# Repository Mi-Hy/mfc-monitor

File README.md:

### 1️⃣ Adjust time to UTC and enable RTC
- `sudo raspi-config`
- `5 Localisation Options` --> `L2 Timezone` --> `None of the above` --> `UTC`
- Reboot Pi `sudo reboot`

### 2️⃣ Create SSH Key to clone this repository
- On the raspberry pi
	```
	ssh-keygen -t ed25519 -C "jarne.vanmulders@kuleuven.be"
	cat ~/.ssh/id_ed25519.pub
	```
- ENTER 3x
- Add key to github account [online] --> settings --> SSH Key
- Clone repo via SSH
- Install git
	```
	sudo apt update
	sudo apt install git -y
	```
- Git clone via SSH KEY on rpi in home dir: `git clone git@github.com:Mi-Hy/mfc-monitor-hw2.git`

### 3️⃣ Enable I2C
- `sudo raspi-config`
- `3 Interface Options` --> `I5 I2C` --> `Yes`
- Check devices on I2C bus
  ```
  sudo apt update
  sudo apt install i2c-tools
  sudo i2cdetect -y 1
  ```
### 4️⃣ Check energy profiler
- Install screen
	```
	sudo apt update
	sudo apt install screen
	```
- `screen /dev/ttyUSB0 115200`

### 5️⃣ Connection with temperature sensors DS18B20
1. Connect D to GPIO4
2. Enable w1-gpio: add `dtoverlay=w1-gpio` with `sudo nano /boot/firmware/config.txt`
3. Reboot `sudo reboot`
4. Activate and test onewire:
	``` 
	sudo modprobe w1-gpio
	sudo modprobe w1-therm
	cd /sys/bus/w1/devices
	ls
	``` 
	If you see the sensor's ID as dir here, all is well. 

### 6️⃣ Install required python packages
Install pip `sudo apt install python3-pip`
```
sudo python3 -m pip install pyyaml --break-system-packages
sudo python3 -m pip install filelock --break-system-packages
sudo python3 -m pip install influxdb_client --break-system-packages
sudo python3 -m pip install flask --break-system-packages
sudo python3 -m pip install psutil --break-system-packages
sudo python3 -m pip install pyserial --break-system-packages
``` 
### 7️⃣ Test all individual scripts
1. Test `system.py`
2. Test `voltages.py`
3. Test `load.py`
4. Test `controller.py`
5. Run services
	1. Copy service files to systemd:
	```
	sudo cp ~/mfc-monitor/controller.service /lib/systemd/system/
 	```
 	2. Enable and start services
  	```
   	sudo systemctl enable controller.service
   	sudo systemctl start controller.service
  	```
   	3. Logs
    ```
   	sudo journalctl -u controller.service -f
    ```
   	4. After updates
	```
	sudo systemctl daemon-reload
	sudo systemctl restart controller.service
 	```

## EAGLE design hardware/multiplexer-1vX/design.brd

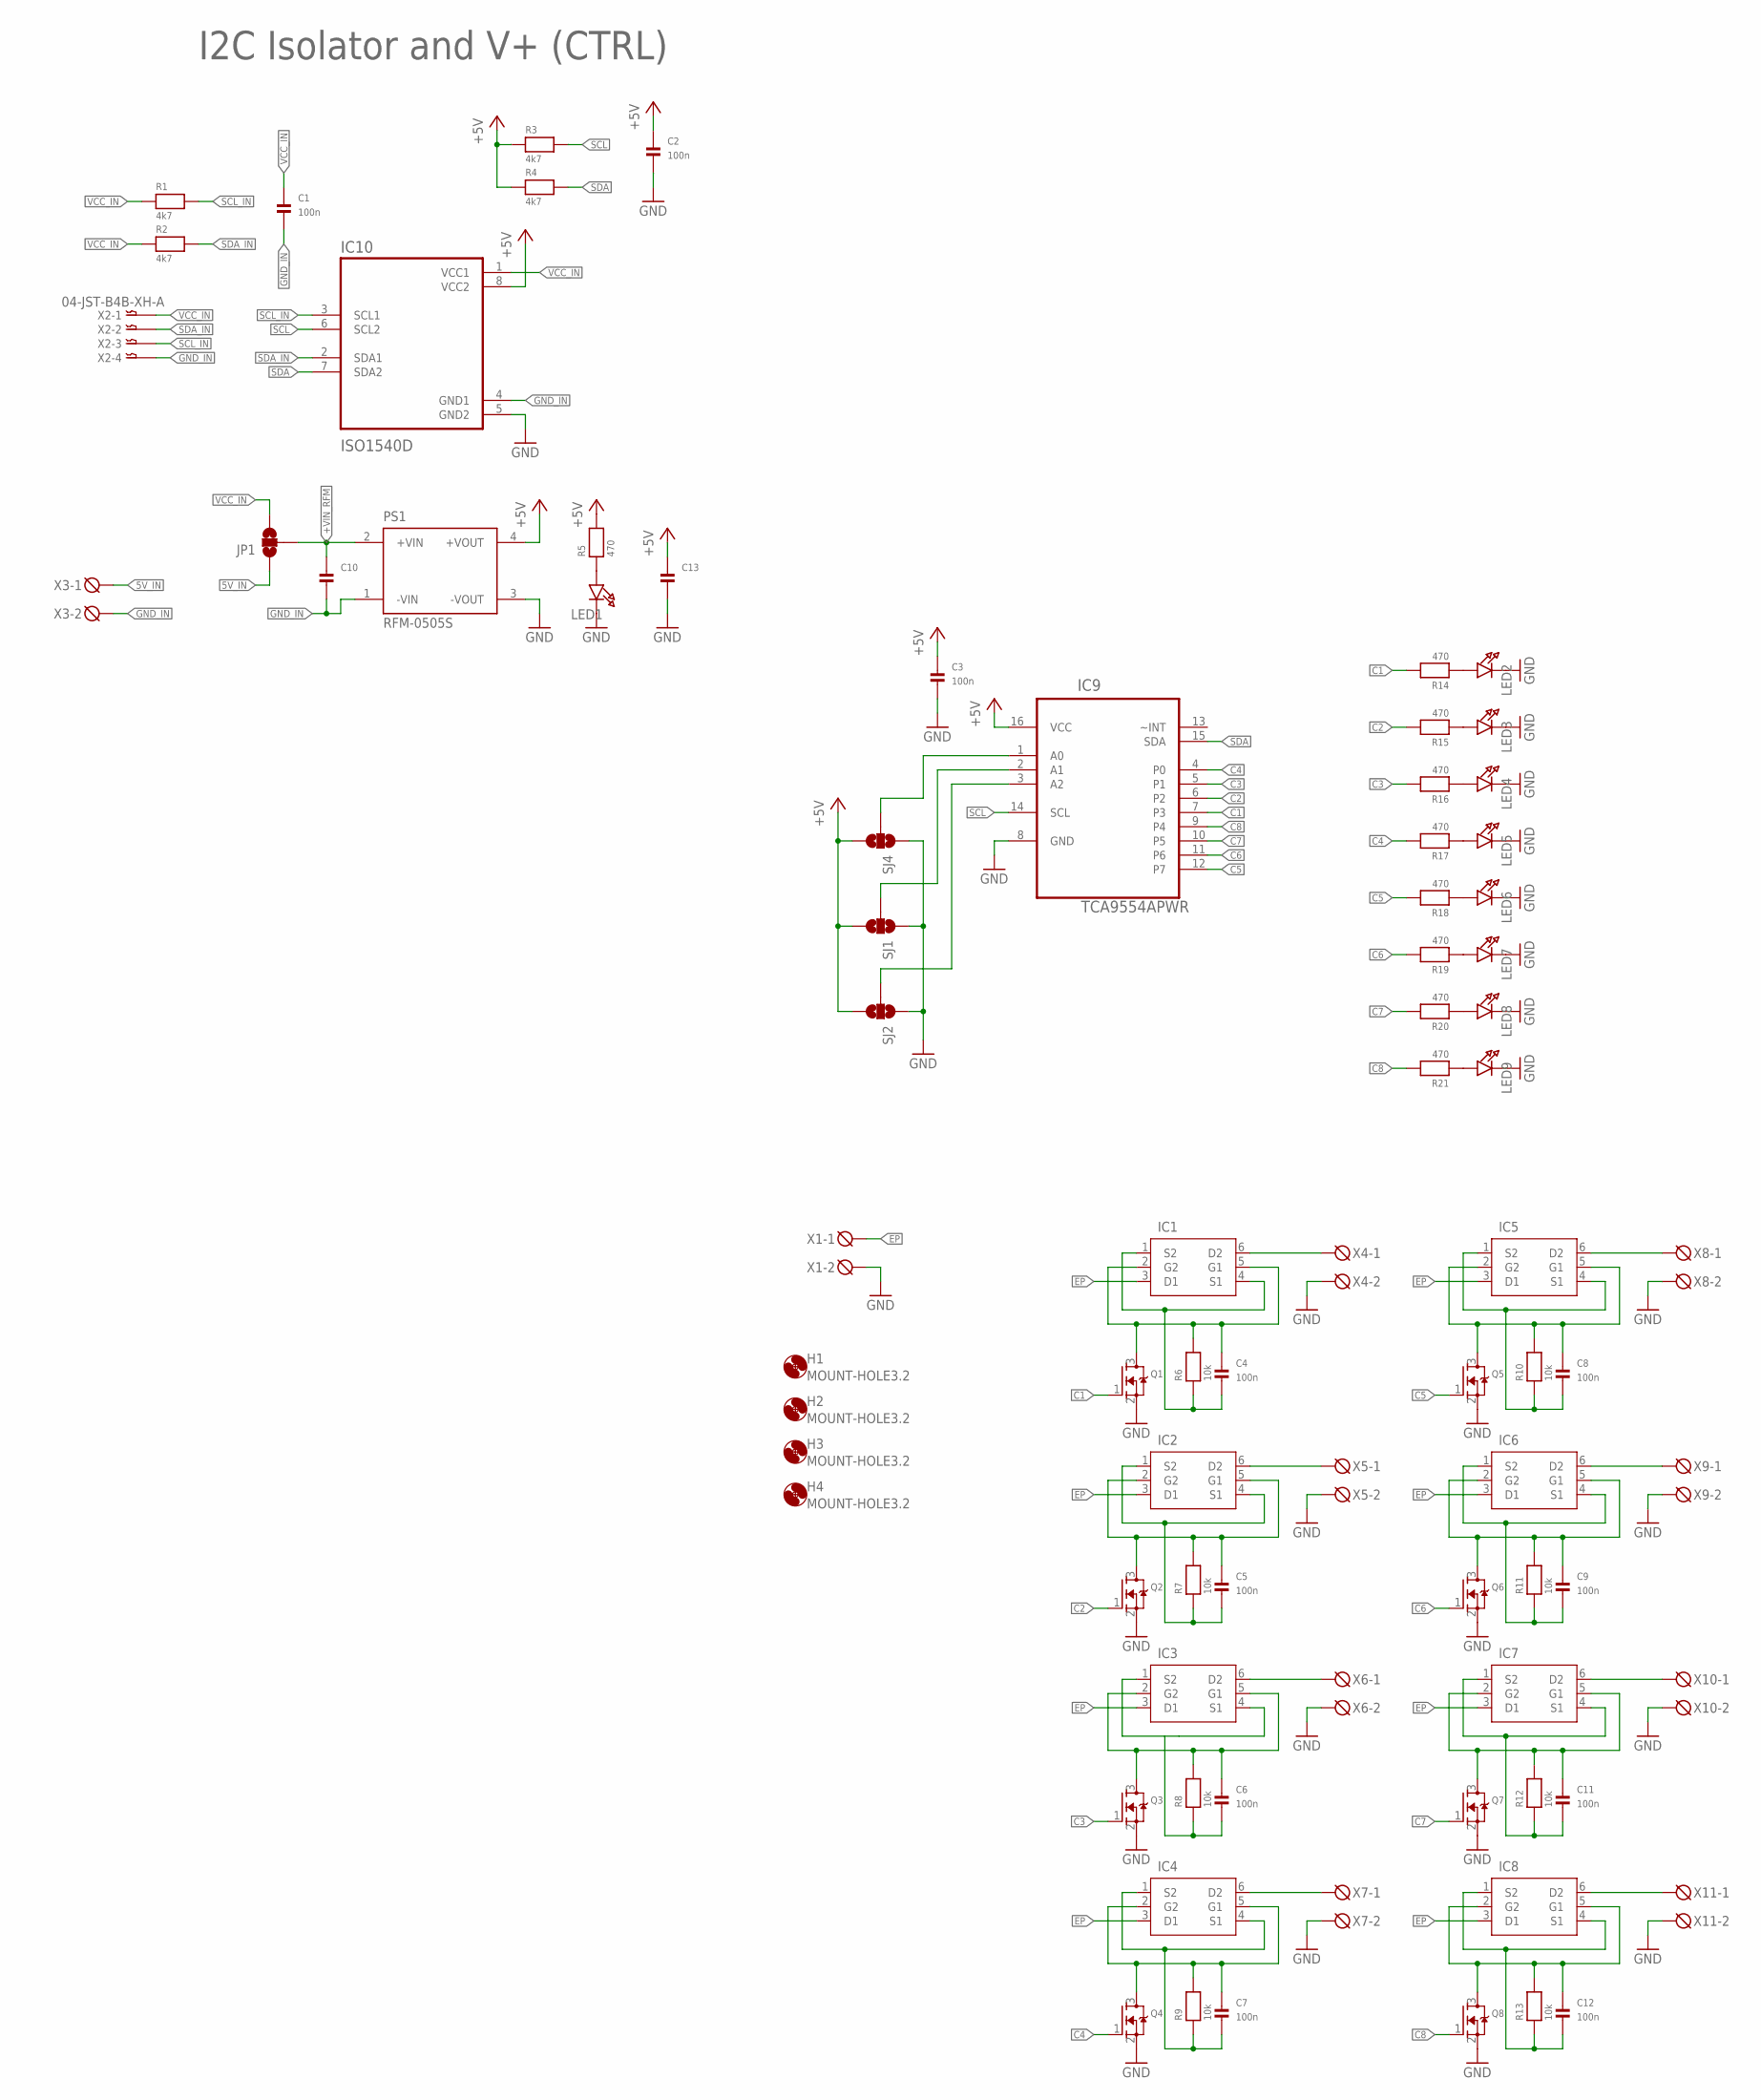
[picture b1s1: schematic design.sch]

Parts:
C1, C2, C3, C4, C5, C6, C7, C8, C9, C11, C12: 100n; 0603
C10, C13: CAP_CERAMIC0805; 0805
H1, H2, H3, H4: MOUNT-HOLE3.2; 3,2
IC1, IC2, IC3, IC4, IC5, IC6, IC7, IC8: DMP2200UDW; SOT65P210X110-6N
IC9: TCA9554APWR; SOP65P640X120-16N
IC10: ISO1540D; SOIC127P599X175-8N
JP1: JUMPER-SMT_3_NO_SILK; SMT-JUMPER_3_NO_SILK
LED1, LED2, LED3, LED4, LED5, LED6, LED7, LED8, LED9: LED0805; CHIPLED_0805
PS1: RFM-0505S; CONV_RFM-0505S
Q1, Q2, Q3, Q4, Q5, Q6, Q7, Q8: MOSFET-NREFLOW; SOT23-R
R1, R2, R3, R4: 4k7; 0603
R5, R14, R15, R16, R17, R18, R19, R20, R21: 470; 0603
R6, R7, R8, R9, R10, R11, R12, R13: 10k; 0603
SJ1, SJ2, SJ4: SOLDERJUMPER_2WAYS; SJ_3
X1, X3, X4, X5, X6, X7, X8, X9, X10, X11: DG3XX-02-5.0; DG306-5.0-02P
X2: 04-JST-B4B-XH-A; B4B-XH

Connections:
5V_IN: JP1.1, X3.1
+5V: C2.1, C3.1, C13.1, IC9.16 (VCC), IC10.8 (VCC2), PS1.4 (+VOUT), R3.1, R4.1, R5.2, SJ1.3, SJ2.3, SJ4.3
+VIN_RFM: C10.1, JP1.2, PS1.2 (+VIN)
C1: IC9.7 (P3), Q1.1 (G), R14.2
C2: IC9.6 (P2), Q2.1 (G), R15.2
C3: IC9.5 (P1), Q3.1 (G), R16.2
C4: IC9.4 (P0), Q4.1 (G), R17.2
C5: IC9.12 (P7), Q5.1 (G), R18.2
C6: IC9.11 (P6), Q6.1 (G), R19.2
C7: IC9.10 (P5), Q7.1 (G), R20.2
C8: IC9.9 (P4), Q8.1 (G), R21.2
EP: IC1.3 (D1), IC2.3 (D1), IC3.3 (D1), IC4.3 (D1), IC5.3 (D1), IC6.3 (D1), IC7.3 (D1), IC8.3 (D1), X1.1
GND: C2.2, C3.2, C13.2, IC9.8 (GND), IC10.5 (GND2), LED1.C, LED2.C, LED3.C, LED4.C, LED5.C, LED6.C, LED7.C, LED8.C, LED9.C, PS1.3 (-VOUT), Q1.2 (S), Q2.2 (S), Q3.2 (S), Q4.2 (S), Q5.2 (S), Q6.2 (S), Q7.2 (S), Q8.2 (S), SJ1.1, SJ2.1, SJ4.1, X1.2, X4.2, X5.2, X6.2, X7.2, X8.2, X9.2, X10.2, X11.2
GND_IN: C1.2, C10.2, IC10.4 (GND1), PS1.1 (-VIN), X2.P$4, X3.2
unnamed: C4.1, IC1.2 (G2), IC1.5 (G1), Q1.3 (D), R6.2
unnamed: C4.2, IC1.1 (S2), IC1.4 (S1), R6.1
unnamed: C5.1, IC2.2 (G2), IC2.5 (G1), Q2.3 (D), R7.2
unnamed: IC1.6 (D2), X4.1
unnamed: IC9.1 (A0), SJ4.2
unnamed: IC9.2 (A1), SJ1.2
unnamed: IC9.3 (A2), SJ2.2
unnamed: IC2.6 (D2), X5.1
unnamed: C5.2, IC2.1 (S2), IC2.4 (S1), R7.1
unnamed: IC3.6 (D2), X6.1
unnamed: C6.2, IC3.1 (S2), IC3.4 (S1), R8.1
unnamed: IC4.6 (D2), X7.1
unnamed: C7.2, IC4.1 (S2), IC4.4 (S1), R9.1
unnamed: IC5.6 (D2), X8.1
unnamed: C8.2, IC5.1 (S2), IC5.4 (S1), R10.1
unnamed: IC6.6 (D2), X9.1
unnamed: C9.2, IC6.1 (S2), IC6.4 (S1), R11.1
unnamed: C11.1, IC7.2 (G2), IC7.5 (G1), Q7.3 (D), R12.2
unnamed: LED1.A, R5.1
unnamed: IC7.6 (D2), X10.1
unnamed: C11.2, IC7.1 (S2), IC7.4 (S1), R12.1
unnamed: IC8.6 (D2), X11.1
unnamed: C12.2, IC8.1 (S2), IC8.4 (S1), R13.1
unnamed: LED2.A, R14.1
unnamed: LED3.A, R15.1
unnamed: LED4.A, R16.1
unnamed: LED5.A, R17.1
unnamed: LED6.A, R18.1
unnamed: LED7.A, R19.1
unnamed: LED8.A, R20.1
unnamed: LED9.A, R21.1
unnamed: C6.1, IC3.2 (G2), IC3.5 (G1), Q3.3 (D), R8.2
unnamed: C7.1, IC4.2 (G2), IC4.5 (G1), Q4.3 (D), R9.2
unnamed: C12.1, IC8.2 (G2), IC8.5 (G1), Q8.3 (D), R13.2
unnamed: C9.1, IC6.2 (G2), IC6.5 (G1), Q6.3 (D), R11.2
unnamed: C8.1, IC5.2 (G2), IC5.5 (G1), Q5.3 (D), R10.2
SCL: IC9.14 (SCL), IC10.6 (SCL2), R3.2
SCL_IN: IC10.3 (SCL1), R1.2, X2.P$3
SDA: IC9.15 (SDA), IC10.7 (SDA2), R4.2
SDA_IN: IC10.2 (SDA1), R2.2, X2.P$2
VCC_IN: C1.1, IC10.1 (VCC1), JP1.3, R1.1, R2.1, X2.P$1

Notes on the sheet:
I2C Isolator and V+ (CTRL)

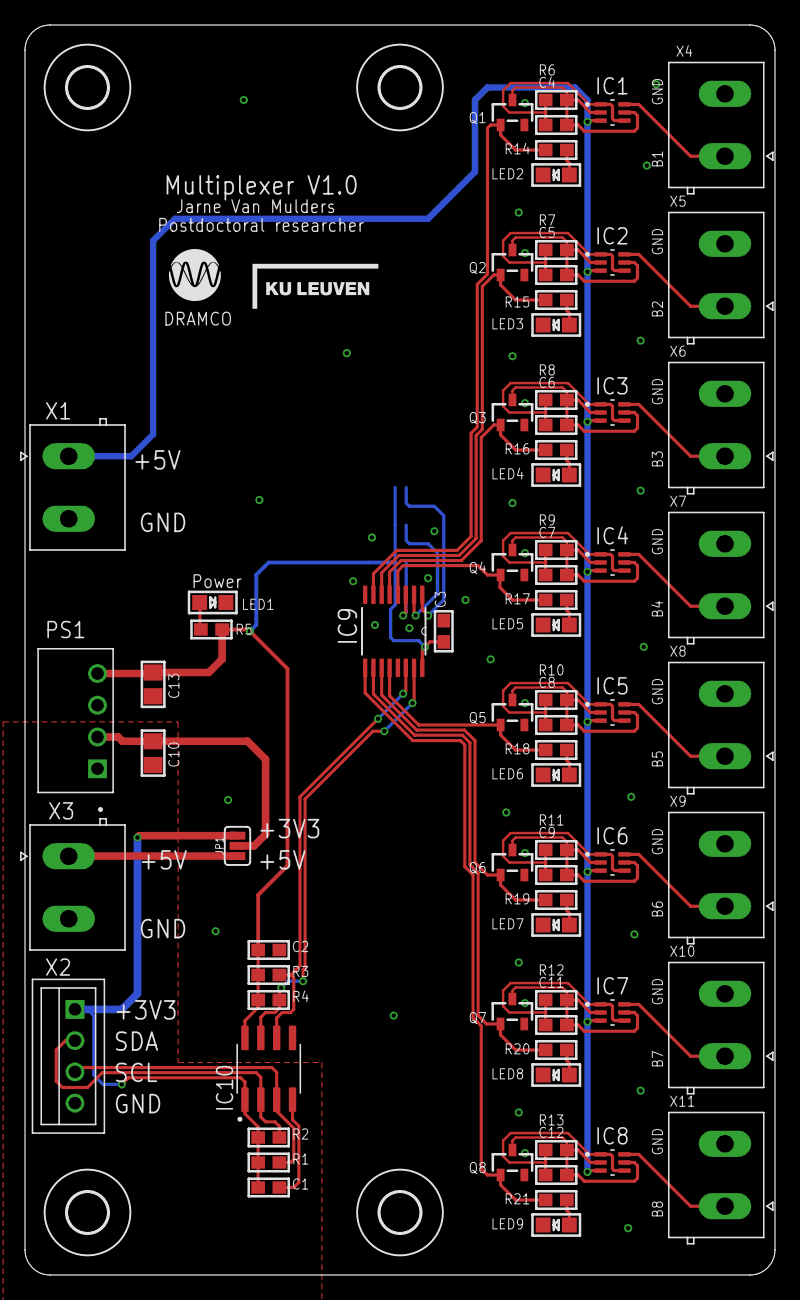
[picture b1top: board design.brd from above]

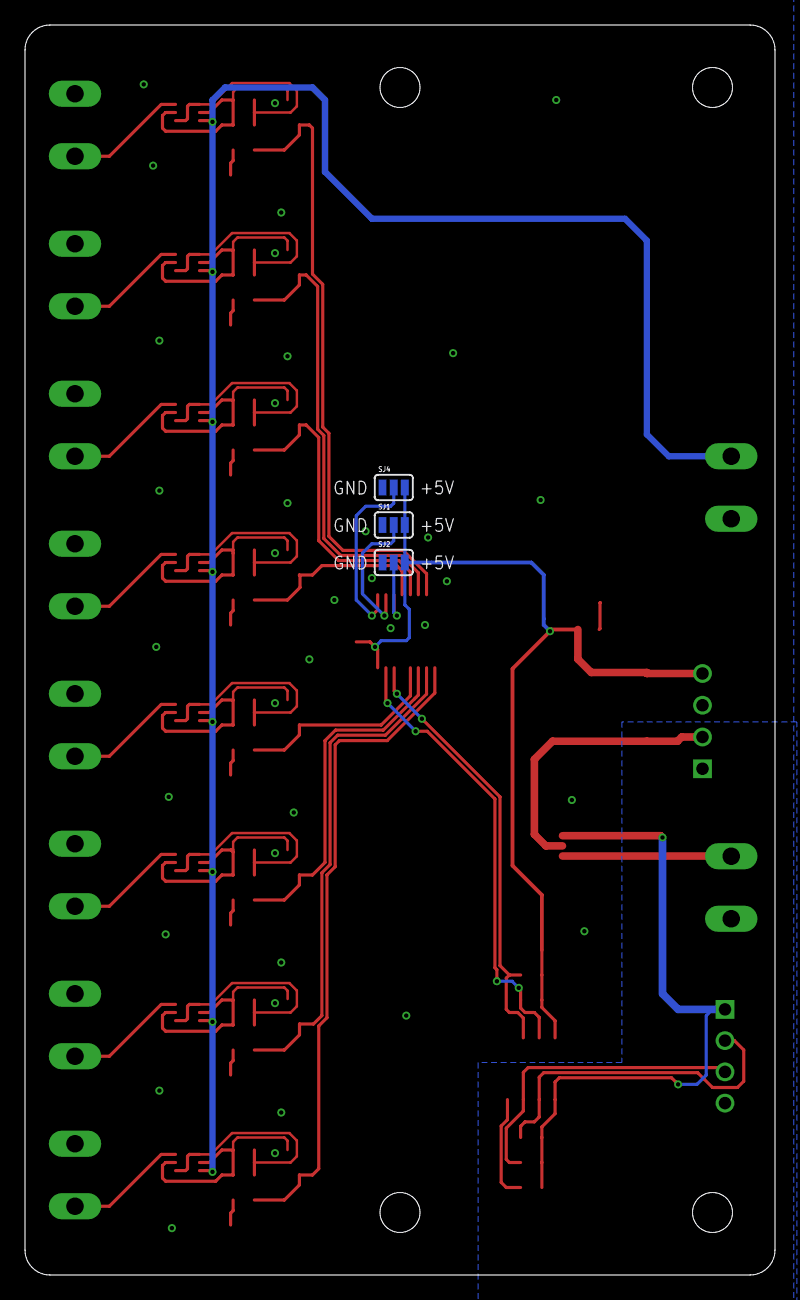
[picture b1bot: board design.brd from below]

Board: 2 copper layers, 60.0 x 100.0 mm, 81 parts (3 on the bottom side), 55 nets.

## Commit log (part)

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2026-04-17 Init commit
2026-04-20 Update HW
2026-04-21 Update hardware
2026-05-18 Include update instructions for controller.service
    Add instructions for updating the service after changes.

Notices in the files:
parts and their libraries:
microbuilder: This work is placed in the public domain, and may be freely used for commercial and non-commercial work with the following conditions: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
SparkFun-Jumpers: Licensing: Creative Commons ShareAlike 4.0 International - https://creativecommons.org/licenses/by-sa/4.0
